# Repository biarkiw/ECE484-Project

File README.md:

# ECE484-Project
Project files for the ECE 484 project, along with the hardware design files for the RPi Pico DSP Hat

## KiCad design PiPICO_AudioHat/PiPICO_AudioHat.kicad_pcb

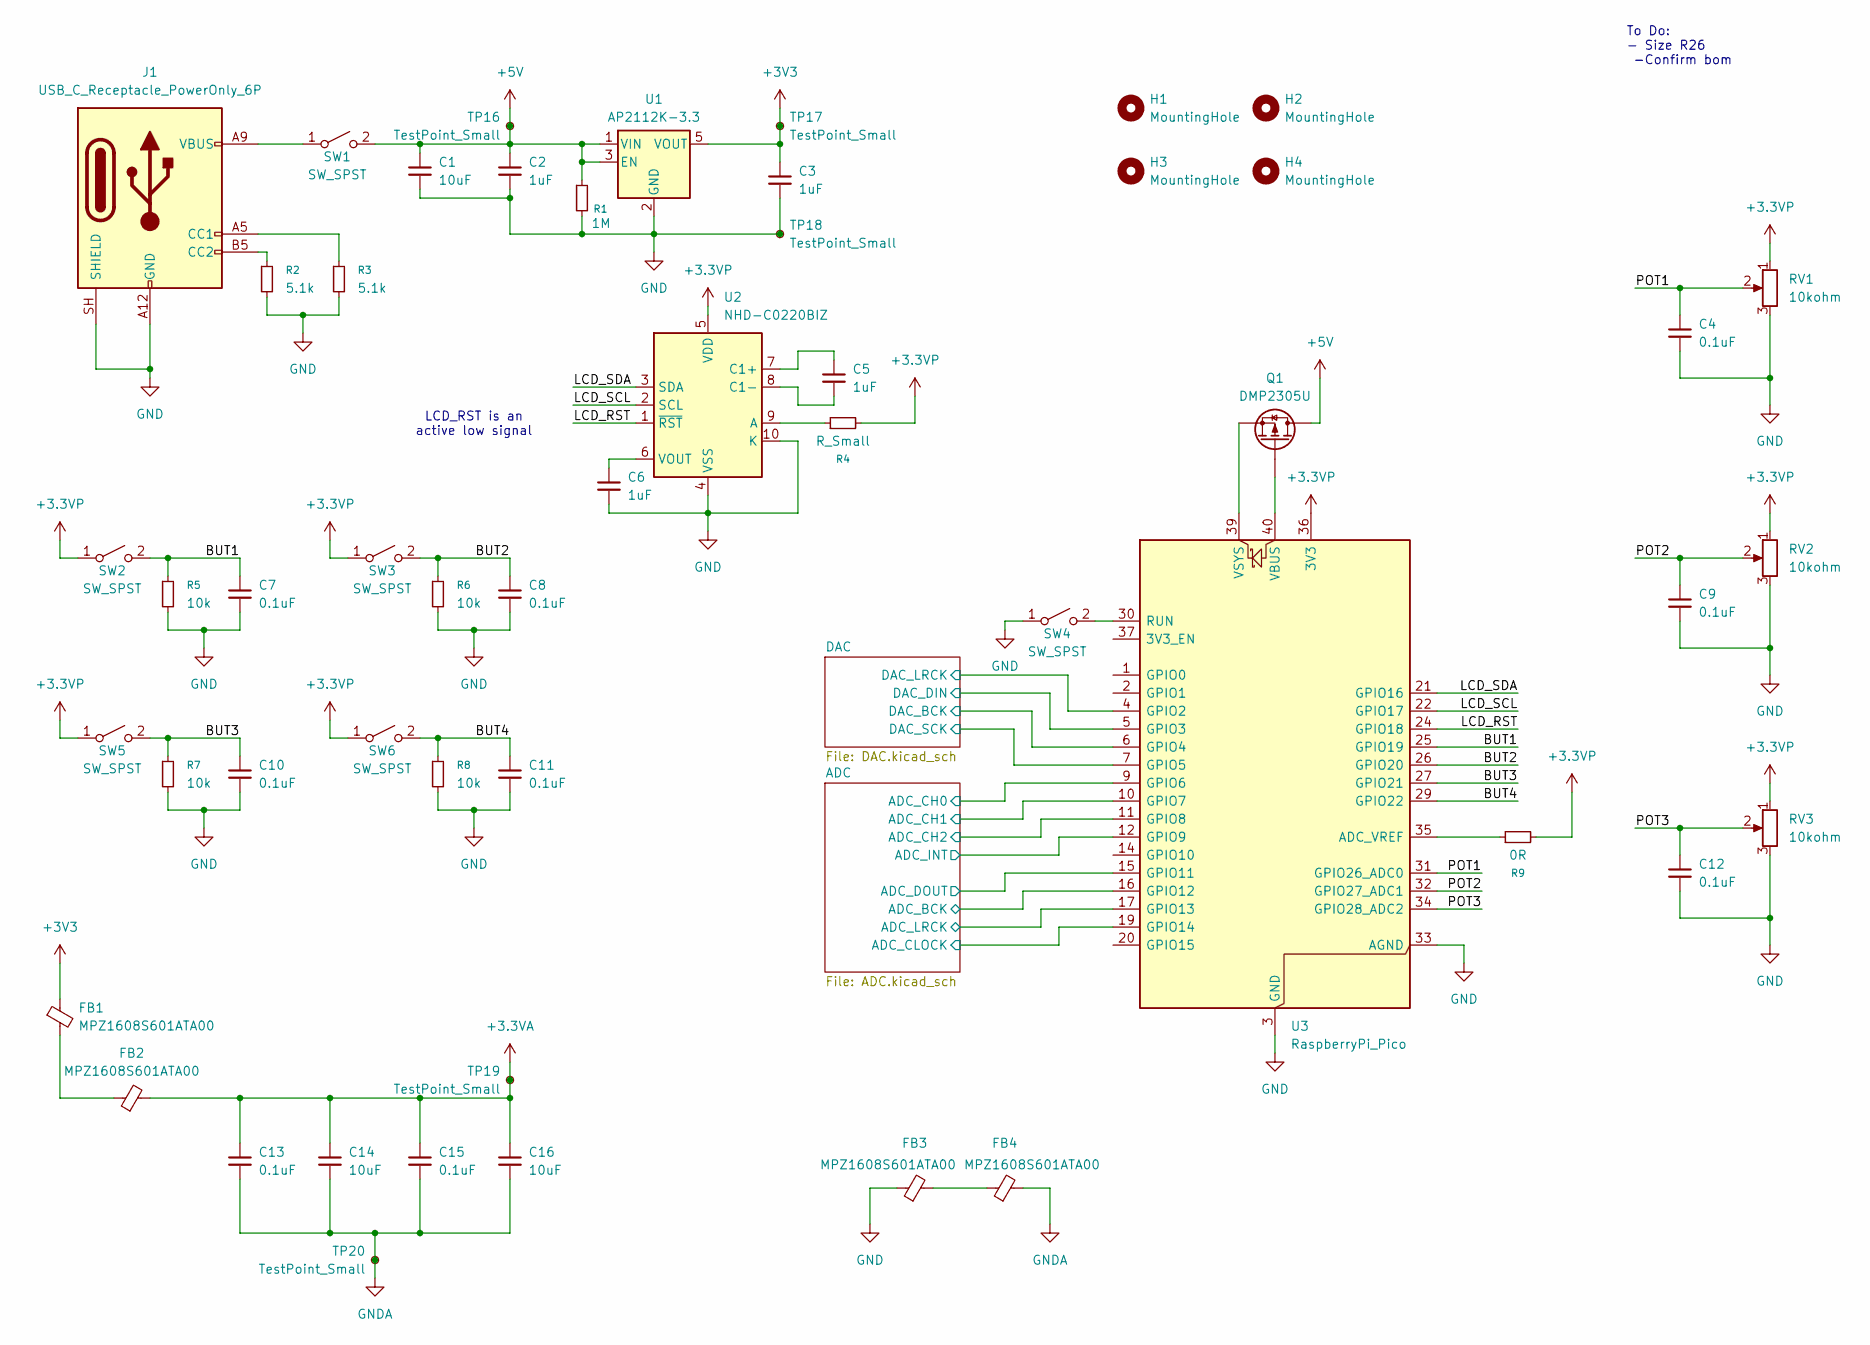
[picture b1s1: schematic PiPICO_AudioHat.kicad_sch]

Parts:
C1, C14, C16: 10uF; C_0805_2012Metric_Pad1.18x1.45mm_HandSolder
C2, C3, C5, C6: 1uF; C_0603_1608Metric_Pad1.08x0.95mm_HandSolder
C4, C7, C8, C9, C10, C11, C12, C13, C15: 0.1uF; C_0603_1608Metric_Pad1.08x0.95mm_HandSolder
FB1, FB2, FB3, FB4: MPZ1608S601ATA00; IND_1608_TDK-M
H1, H2, H3, H4: MountingHole; MountingHole_4.3mm_M4_ISO7380_Pad
J1: USB_C_Receptacle_PowerOnly_6P; SAMESKY_UJC-H-G-SMT-2-P6-TR
Q1: DMP2305U; TSOT-23_HandSoldering
R1: 1M; R_0603_1608Metric_Pad0.98x0.95mm_HandSolder
R2, R3: 5.1k; R_0603_1608Metric_Pad0.98x0.95mm_HandSolder
R4: R_Small; R_0603_1608Metric_Pad0.98x0.95mm_HandSolder
R5, R6, R7, R8: 10k; R_0603_1608Metric_Pad0.98x0.95mm_HandSolder
R9: 0R; R_0603_1608Metric_Pad0.98x0.95mm_HandSolder
RV1, RV2, RV3: 10kohm; TRIM_PT01-D115D-B503
SW1: SW_SPST; SW_500SSP1S1M6QEA
SW2, SW3, SW4, SW5, SW6: SW_SPST; SW_TL3305BF260QG
TP16, TP17, TP18, TP19, TP20: TestPoint_Small; TestPoint_Loop_D2.60mm_Drill0.9mm_Beaded
U1: AP2112K-3.3; SOT-23-5
U2: NHD-C0220BIZ; NHD-C0220BiZ
U3: RaspberryPi_Pico; RaspberryPi_Pico_Common_Unspecified

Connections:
+3.3VA: C13.2, C14.1, C15.2, C16.1, FB2.2, TP19.1 (1_1); also elsewhere on the board
+3.3VP: R4.2, R9.2, RV1.1, RV2.1, RV3.1, SW2.1 (A), SW3.1 (A), SW5.1 (A), SW6.1 (A), U2.5 (VDD), U3.36 (3V3)
+3V3: C3.1, FB1.1, TP17.1 (1_1), U1.5 (VOUT); also elsewhere on the board
+5V: C1.1, C2.1, Q1.3 (D), R1.1, SW1.2 (B), TP16.1 (1_1), U1.1 (VIN), U1.3 (EN)
/ADC/ADC_BCK: U3.16 (GPIO12); also elsewhere on the board
/ADC/ADC_CH0: U3.9 (GPIO6); also elsewhere on the board
/ADC/ADC_CH1: U3.10 (GPIO7); also elsewhere on the board
/ADC/ADC_CH2: U3.11 (GPIO8); also elsewhere on the board
/ADC/ADC_CLOCK: U3.19 (GPIO14); also elsewhere on the board
/ADC/ADC_DOUT: U3.15 (GPIO11); also elsewhere on the board
/ADC/ADC_INT: U3.12 (GPIO9); also elsewhere on the board
/ADC/ADC_LRCK: U3.17 (GPIO13); also elsewhere on the board
/BUT1: C7.1, R5.1, SW2.2 (B), U3.25 (GPIO19)
/BUT2: C8.1, R6.1, SW3.2 (B), U3.26 (GPIO20)
/BUT3: C10.1, R7.1, SW5.2 (B), U3.27 (GPIO21)
/BUT4: C11.1, R8.1, SW6.2 (B), U3.29 (GPIO22)
/DAC/DAC_BCK: U3.6 (GPIO4); also elsewhere on the board
/DAC/DAC_DIN: U3.5 (GPIO3); also elsewhere on the board
/DAC/DAC_LRCK: U3.4 (GPIO2); also elsewhere on the board
/DAC/DAC_SCK: U3.7 (GPIO5); also elsewhere on the board
/LCD_RST: U2.1 (~RST), U3.24 (GPIO18)
/LCD_SCL: U2.2 (SCL), U3.22 (GPIO17)
/LCD_SDA: U2.3 (SDA), U3.21 (GPIO16)
/POT1: C4.1, RV1.2, U3.31 (GPIO26_ADC0)
/POT2: C9.1, RV2.2, U3.32 (GPIO27_ADC1)
/POT3: C12.1, RV3.2, U3.34 (GPIO28_ADC2)
GND: C1.2, C2.2, C3.2, C4.2, C6.2, C7.2, C8.2, C9.2, C10.2, C11.2, C12.2, FB3.1, J1.A12 (GND), J1.B12 (GND), J1.SH (SHIELD), R1.2, R2.2, R3.2, R5.2, R6.2, R7.2, R8.2, RV1.3, RV2.3, RV3.3, SW4.1 (A), TP18.1 (1_1), U1.2 (GND), U2.4 (VSS), U2.10 (K), U3.3 (GND), U3.8 (GND), U3.13 (GND), U3.18 (GND), U3.23 (GND), U3.28 (GND), U3.33 (AGND), U3.38 (GND); also elsewhere on the board
GNDA: C13.1, C14.2, C15.1, C16.2, FB4.2, TP20.1 (1_1); also elsewhere on the board
unnamed: FB1.2, FB2.1
unnamed: FB3.2, FB4.1
unnamed: J1.A5 (CC1), R3.1
unnamed: J1.B5 (CC2), R2.1
unnamed: Q1.1 (G), U3.40 (VBUS)
unnamed: Q1.2 (S), U3.39 (VSYS)
unnamed: J1.A9 (VBUS), J1.B9 (VBUS), SW1.1 (A)
unnamed: SW4.2 (B), U3.30 (RUN)
unnamed: R4.1, U2.9 (A)
unnamed: C5.1, U2.7 (C1+)
unnamed: C5.2, U2.8 (C1-)
unnamed: C6.1, U2.6 (VOUT)
unnamed: R9.1, U3.35 (ADC_VREF)

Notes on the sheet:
To Do: - Size R26 -Confirm bom
LCD_RST is an active low signal

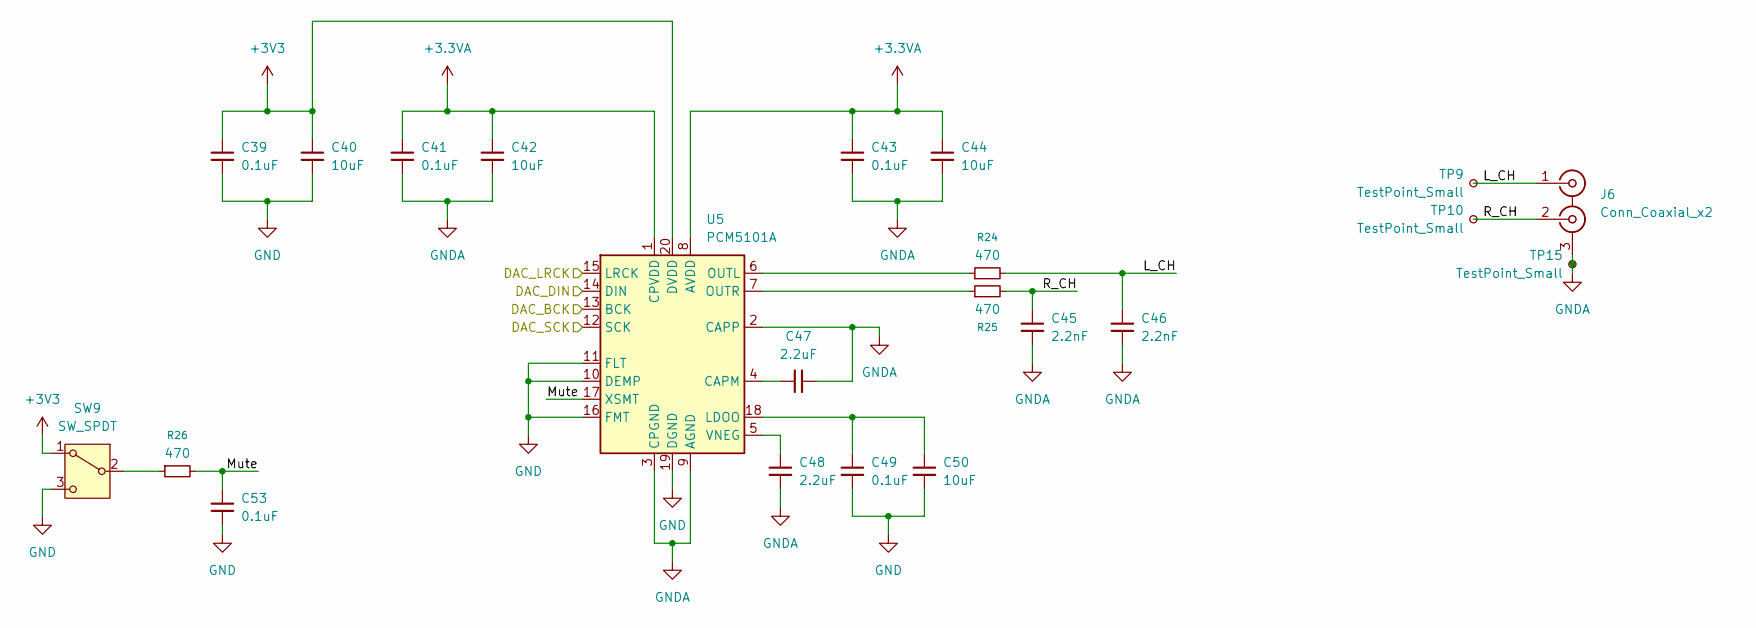
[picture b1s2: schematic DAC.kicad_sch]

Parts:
C39, C41, C43, C49, C53: 0.1uF; C_0603_1608Metric_Pad1.08x0.95mm_HandSolder
C40, C42, C44, C50: 10uF; C_0805_2012Metric_Pad1.18x1.45mm_HandSolder
C45, C46: 2.2nF; C_0603_1608Metric_Pad1.08x0.95mm_HandSolder
C47, C48: 2.2uF; C_0603_1608Metric_Pad1.08x0.95mm_HandSolder
J6: Conn_Coaxial_x2; SAMESKY_RCJ-2223
R24, R25, R26: 470; R_0603_1608Metric_Pad0.98x0.95mm_HandSolder
SW9: SW_SPDT; SW_JS102011SAQN
TP9, TP10, TP15: TestPoint_Small; TestPoint_Loop_D2.60mm_Drill0.9mm_Beaded
U5: PCM5101A; TSSOP-20_4.4x6.5mm_P0.65mm

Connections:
+3.3VA: C41.1, C42.1, C43.1, C44.1, U5.1 (CPVDD), U5.8 (AVDD); also elsewhere on the board
+3V3: C39.1, C40.1, SW9.1 (A), U5.20 (DVDD); also elsewhere on the board
/DAC/DAC_BCK: U5.13 (BCK); also elsewhere on the board
/DAC/DAC_DIN: U5.14 (DIN); also elsewhere on the board
/DAC/DAC_LRCK: U5.15 (LRCK); also elsewhere on the board
/DAC/DAC_SCK: U5.12 (SCK); also elsewhere on the board
/DAC/L_CH: C46.1, J6.1 (IN1), R24.2, TP9.1 (1_1)
/DAC/Mute: C53.1, R26.2, U5.17 (XSMT)
/DAC/R_CH: C45.1, J6.2 (IN2), R25.2, TP10.1 (1_1)
GND: C39.2, C40.2, C49.2, C50.2, C53.2, SW9.3 (C), U5.10 (DEMP), U5.11 (FLT), U5.16 (FMT), U5.19 (DGND); also elsewhere on the board
GNDA: C41.2, C42.2, C43.2, C44.2, C45.2, C46.2, C47.2, C48.2, J6.3 (EXT), TP15.1 (1_1), U5.2 (CAPP), U5.3 (CPGND), U5.9 (AGND); also elsewhere on the board
unnamed: R26.1, SW9.2 (B)
unnamed: C47.1, U5.4 (CAPM)
unnamed: C49.1, C50.1, U5.18 (LDOO)
unnamed: R24.1, U5.6 (OUTL)
unnamed: R25.1, U5.7 (OUTR)
unnamed: C48.1, U5.5 (VNEG)

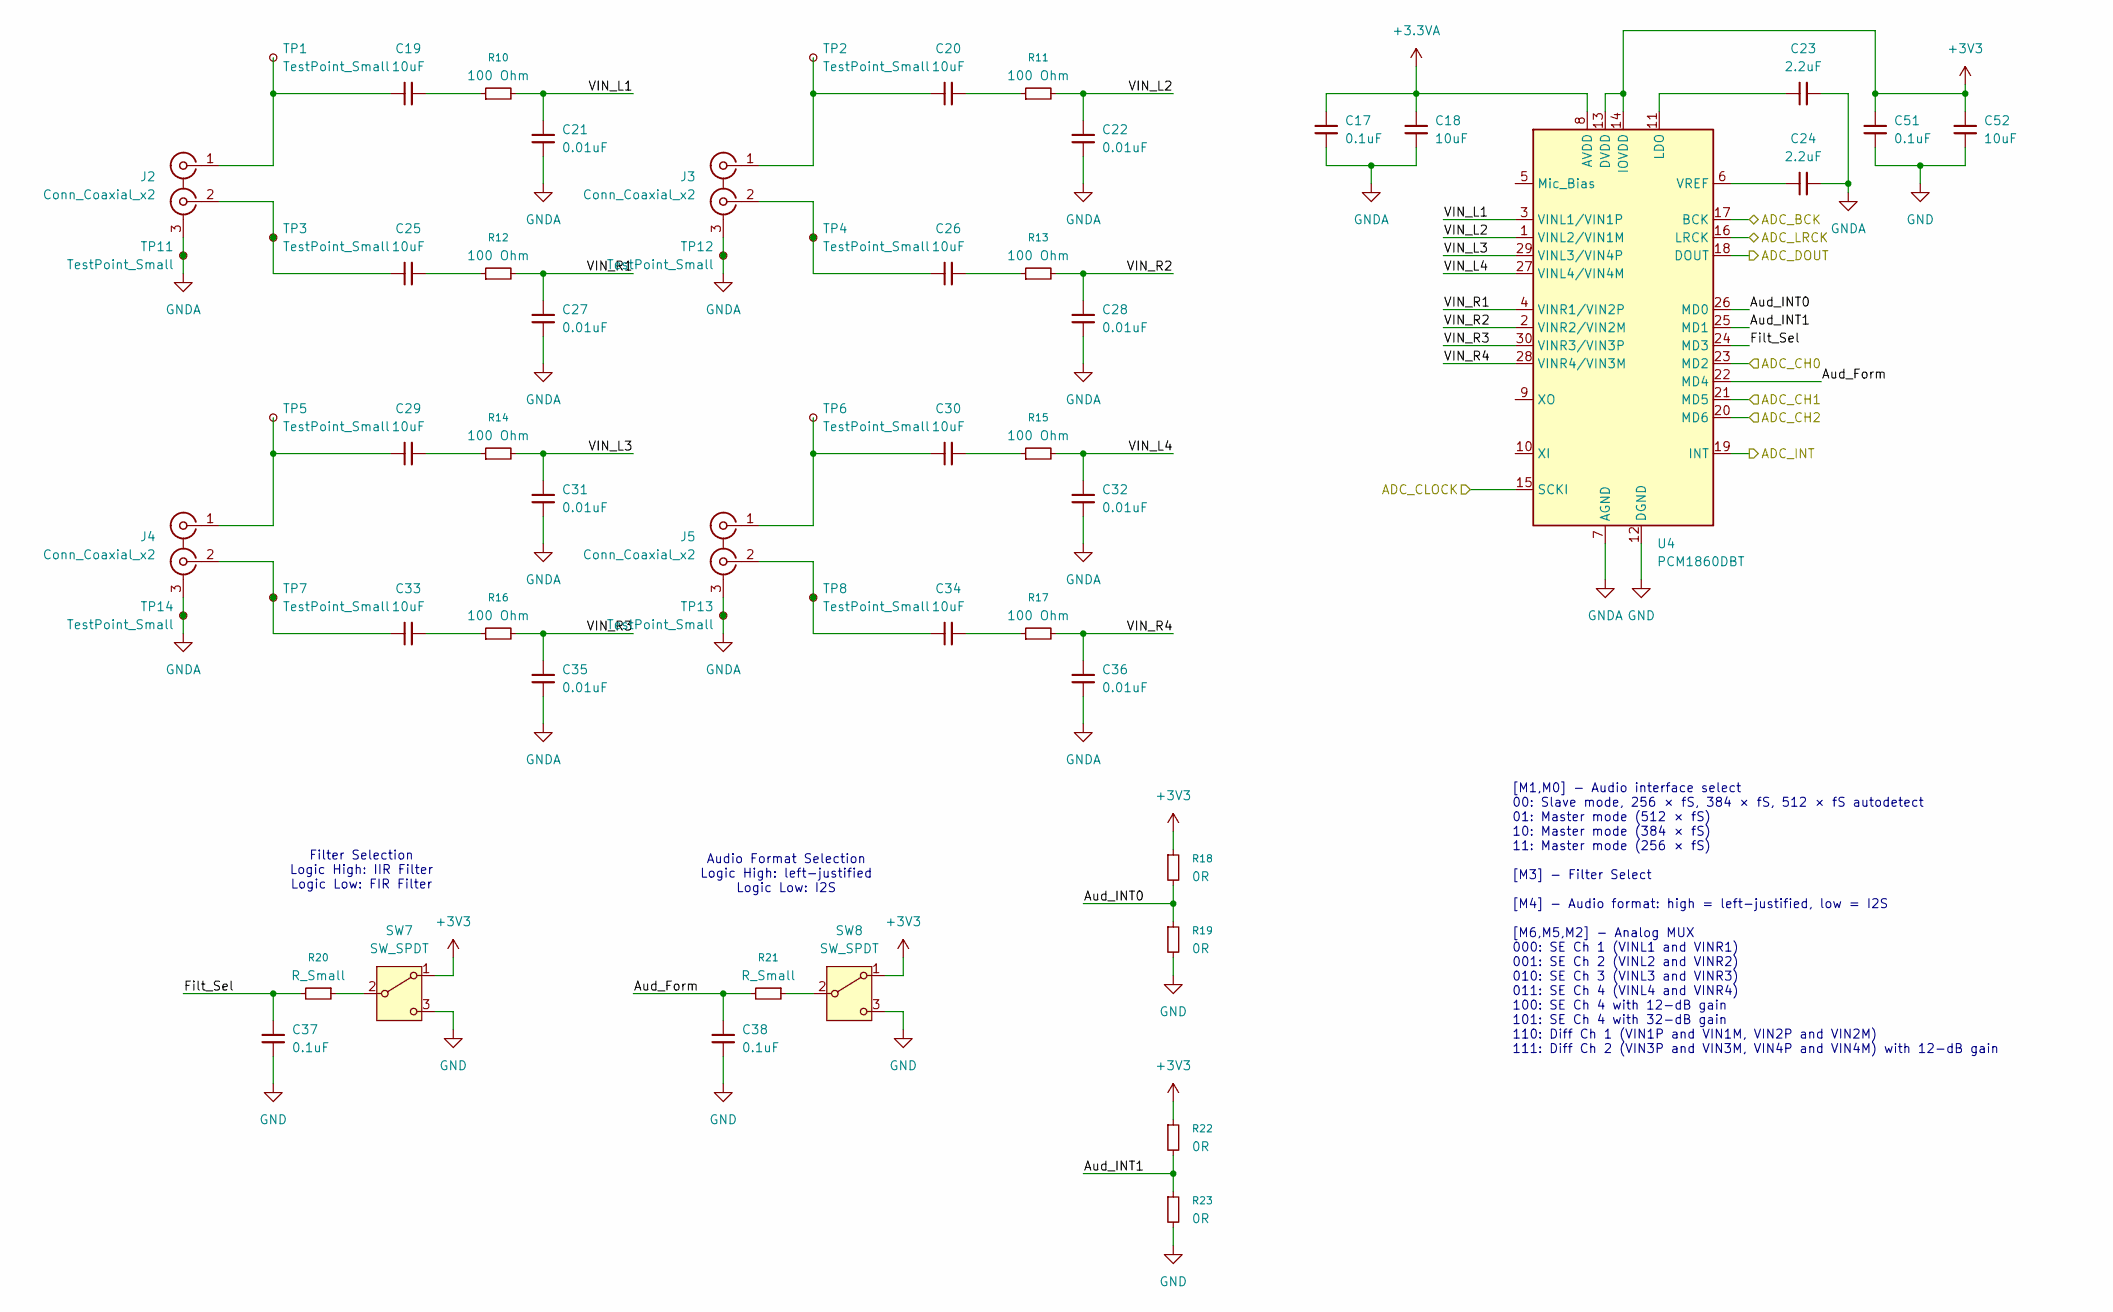
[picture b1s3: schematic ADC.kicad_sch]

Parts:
C17, C37, C38, C51: 0.1uF; C_0603_1608Metric_Pad1.08x0.95mm_HandSolder
C18, C19, C20, C25, C26, C29, C30, C33, C34, C52: 10uF; C_0805_2012Metric_Pad1.18x1.45mm_HandSolder
C21, C22, C27, C28, C31, C32, C35, C36: 0.01uF; C_0603_1608Metric_Pad1.08x0.95mm_HandSolder
C23, C24: 2.2uF; C_0603_1608Metric_Pad1.08x0.95mm_HandSolder
J2, J3, J4, J5: Conn_Coaxial_x2; SAMESKY_RCJ-2223
R10, R11, R12, R13, R14, R15, R16, R17: 100 Ohm; R_0603_1608Metric_Pad0.98x0.95mm_HandSolder
R18, R19, R22, R23: 0R; R_0603_1608Metric_Pad0.98x0.95mm_HandSolder
R20, R21: R_Small; R_0603_1608Metric_Pad0.98x0.95mm_HandSolder
SW7, SW8: SW_SPDT; SW_JS102011SAQN
TP1, TP2, TP3, TP4, TP5, TP6, TP7, TP8, TP11, TP12, TP13, TP14: TestPoint_Small; TestPoint_Loop_D2.60mm_Drill0.9mm_Beaded
U4: PCM1860DBT; TSSOP-30_4.4x7.8mm_P0.5mm

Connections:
+3.3VA: C17.2, C18.1, U4.8 (AVDD); also elsewhere on the board
+3V3: C51.2, C52.1, R18.1, R22.1, SW7.1 (A), SW8.1 (A), U4.13 (DVDD), U4.14 (IOVDD); also elsewhere on the board
/ADC/ADC_BCK: U4.17 (BCK); also elsewhere on the board
/ADC/ADC_CH0: U4.23 (MD2); also elsewhere on the board
/ADC/ADC_CH1: U4.21 (MD5); also elsewhere on the board
/ADC/ADC_CH2: U4.20 (MD6); also elsewhere on the board
/ADC/ADC_CLOCK: U4.15 (SCKI); also elsewhere on the board
/ADC/ADC_DOUT: U4.18 (DOUT); also elsewhere on the board
/ADC/ADC_INT: U4.19 (INT); also elsewhere on the board
/ADC/ADC_LRCK: U4.16 (LRCK); also elsewhere on the board
/ADC/Aud_Form: C38.1, R21.2, U4.22 (MD4)
/ADC/Aud_INT0: R18.2, R19.1, U4.26 (MD0)
/ADC/Aud_INT1: R22.2, R23.1, U4.25 (MD1)
/ADC/Filt_Sel: C37.1, R20.2, U4.24 (MD3)
/ADC/VIN_L1: C21.2, R10.2, U4.3 (VINL1/VIN1P)
/ADC/VIN_L2: C22.2, R11.2, U4.1 (VINL2/VIN1M)
/ADC/VIN_L3: C31.2, R14.2, U4.29 (VINL3/VIN4P)
/ADC/VIN_L4: C32.2, R15.2, U4.27 (VINL4/VIN4M)
/ADC/VIN_R1: C27.2, R12.2, U4.4 (VINR1/VIN2P)
/ADC/VIN_R2: C28.2, R13.2, U4.2 (VINR2/VIN2M)
/ADC/VIN_R3: C35.2, R16.2, U4.30 (VINR3/VIN3P)
/ADC/VIN_R4: C36.2, R17.2, U4.28 (VINR4/VIN3M)
GND: C37.2, C38.2, C51.1, C52.2, R19.2, R23.2, SW7.3 (C), SW8.3 (C), U4.12 (DGND); also elsewhere on the board
GNDA: C17.1, C18.2, C21.1, C22.1, C23.2, C24.2, C27.1, C28.1, C31.1, C32.1, C35.1, C36.1, J2.3 (EXT), J3.3 (EXT), J4.3 (EXT), J5.3 (EXT), TP11.1 (1_1), TP12.1 (1_1), TP13.1 (1_1), TP14.1 (1_1), U4.7 (AGND); also elsewhere on the board
unnamed: C19.2, R10.1
unnamed: C20.2, R11.1
unnamed: C25.2, R12.1
unnamed: C26.2, R13.1
unnamed: C29.2, R14.1
unnamed: C30.2, R15.1
unnamed: C33.2, R16.1
unnamed: C34.2, R17.1
unnamed: C19.1, J2.1 (IN1), TP1.1 (1_1)
unnamed: C25.1, J2.2 (IN2), TP3.1 (1_1)
unnamed: C20.1, J3.1 (IN1), TP2.1 (1_1)
unnamed: C26.1, J3.2 (IN2), TP4.1 (1_1)
unnamed: C29.1, J4.1 (IN1), TP5.1 (1_1)
unnamed: C33.1, J4.2 (IN2), TP7.1 (1_1)
unnamed: C30.1, J5.1 (IN1), TP6.1 (1_1)
unnamed: C34.1, J5.2 (IN2), TP8.1 (1_1)
unnamed: R20.1, SW7.2 (B)
unnamed: R21.1, SW8.2 (B)
unnamed: C23.1, U4.11 (LDO)
unnamed: C24.1, U4.6 (VREF)

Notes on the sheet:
Audio Format Selection Logic High: left-justified Logic Low: I2S
[M1,M0] - Audio interface select 00: Slave mode, 256 × fS, 384 × fS, 512 × fS autodetect 01: Master mode (512 × fS) 10: Master mode (384 × fS) 11: Master mode (256 × fS) [M3] - Filter Select [M4] - Audio format: high = left-justified, low = I2S [M6,M5,M2] - Analog MUX 000: SE Ch 1 (VINL1 and VINR1)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
Filter Selection Logic High: IIR Filter Logic Low: FIR Filter

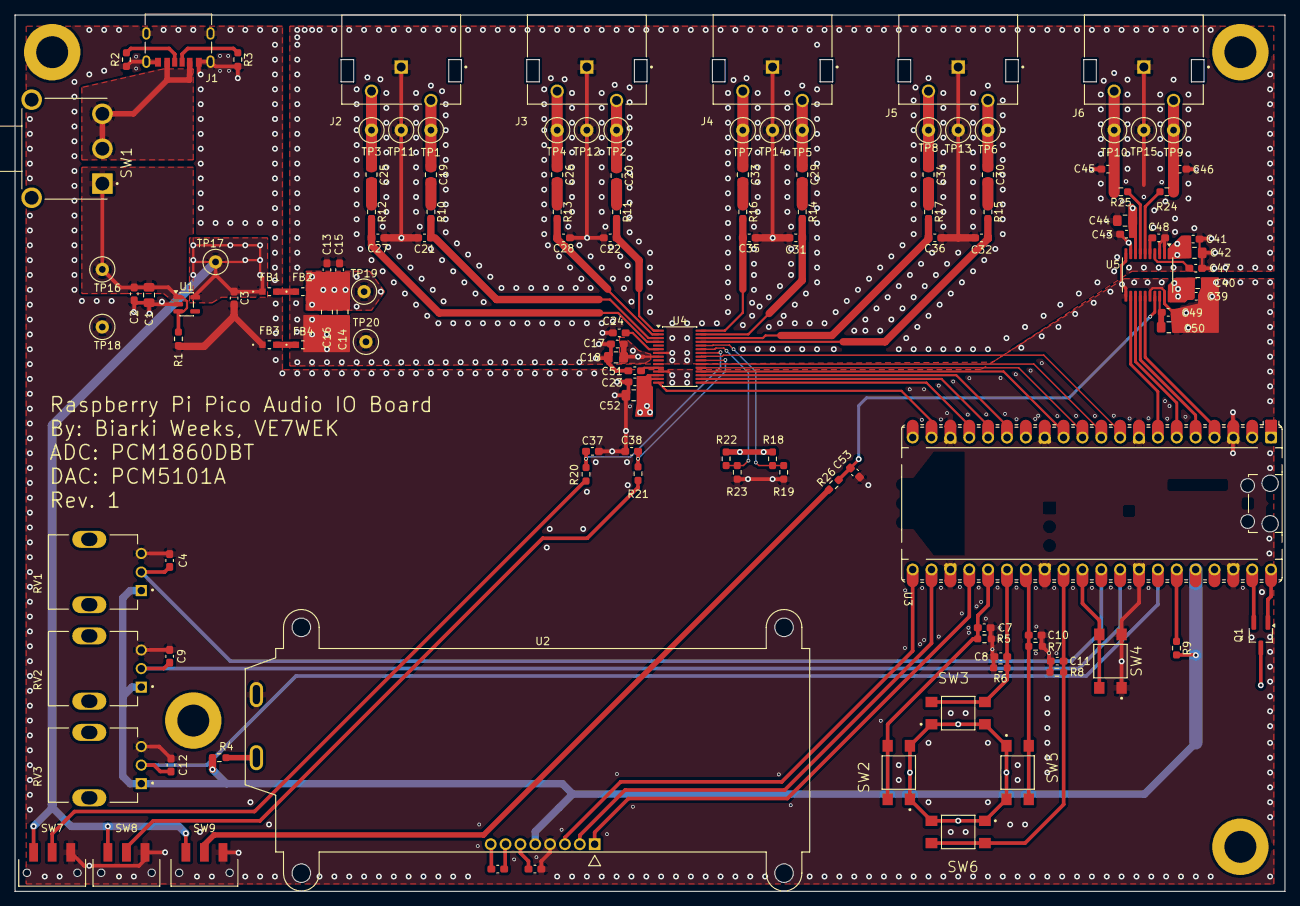
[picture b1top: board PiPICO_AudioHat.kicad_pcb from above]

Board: 4 copper layers, 171.0 x 118.0 mm, 131 parts (0 on the bottom side), 82 nets.
